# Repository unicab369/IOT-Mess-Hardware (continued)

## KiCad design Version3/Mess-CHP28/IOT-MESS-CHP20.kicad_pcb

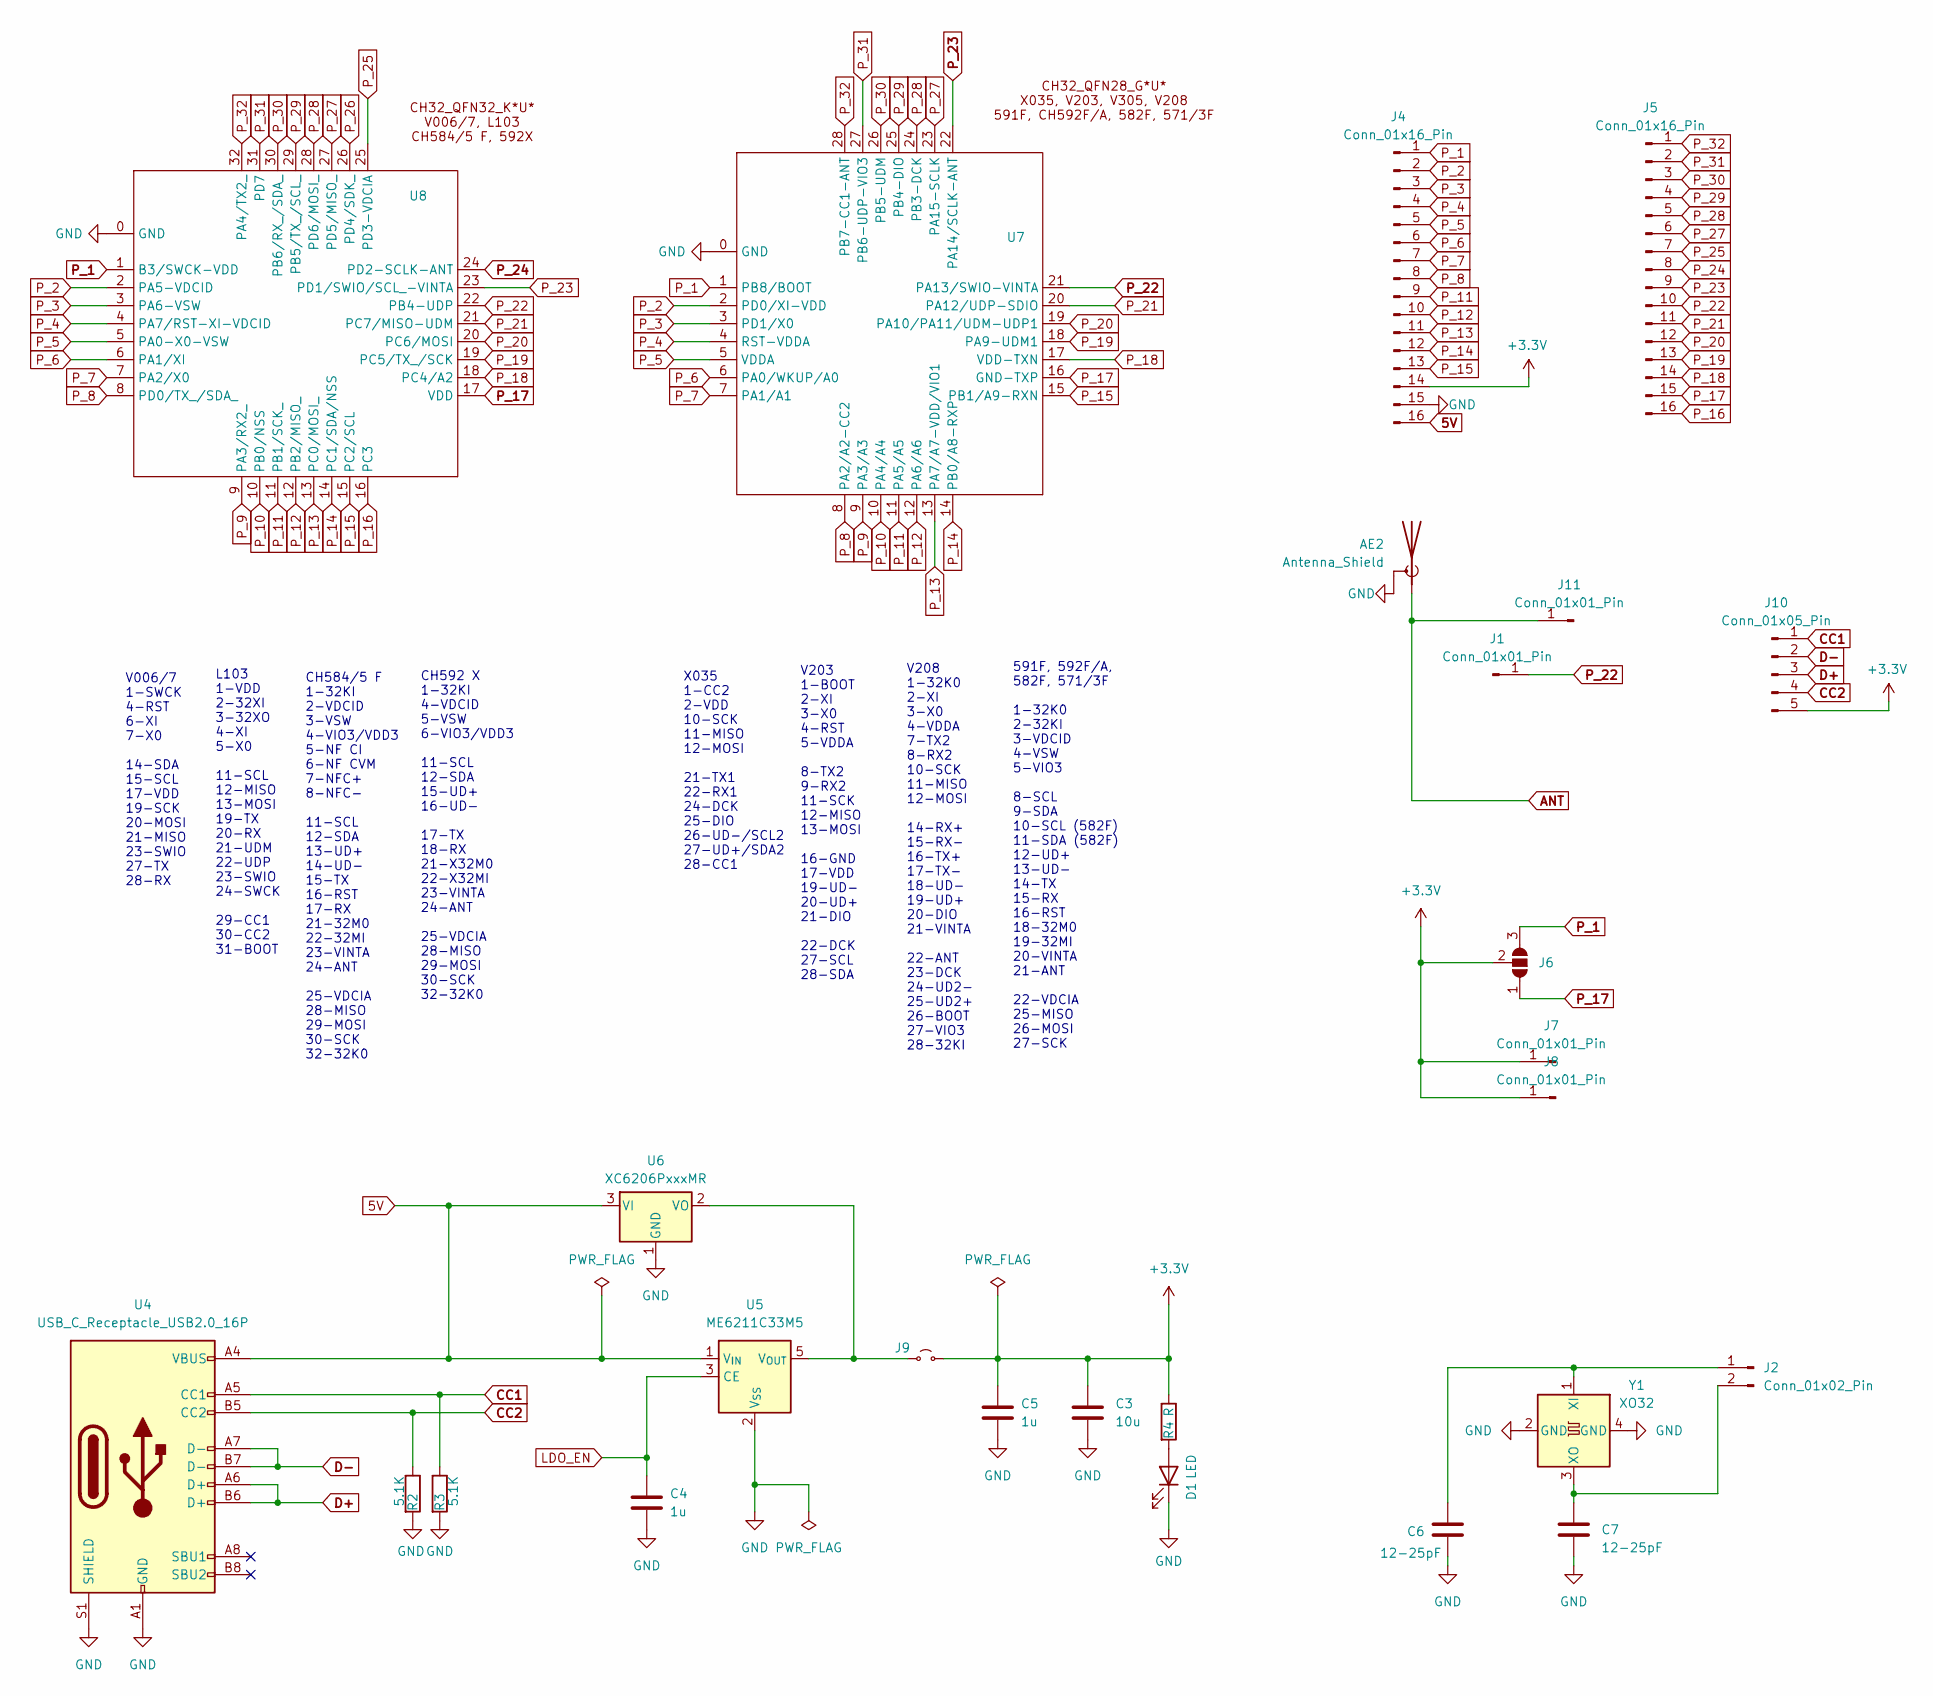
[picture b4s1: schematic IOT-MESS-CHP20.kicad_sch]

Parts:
AE2: Antenna_Shield; Texas_SWRA117D_2.4GHz_Left
C3: 10u; C_0603_1608Metric
C4, C5: 1u; C_0603_1608Metric
C6, C7: 12-25pF; C_0603_1608Metric
D1: LED; LED_0603_1608Metric
J1, J7, J8, J11: Conn_01x01_Pin; PinHeader_1x01_P1.00mm_Vertical
J2: Conn_01x02_Pin; PinHeader_1x02_P1.27mm_Vertical
J4, J5: Conn_01x16_Pin; PinHeader_1x16_P2.54mm_Vertical
J6: Jumper; Jumper-3_P1.3mm_Open_RoundedPad1.0x1.5mm
J9: Jumper_2; Jumpper-triangle
J10: Conn_01x05_Pin; PinHeader_1x05_P1.27mm_Vertical
R2, R3: 5.1K; R_0603_1608Metric
R4: R; R_0603_1608Metric
U4: USB_C_Receptacle_USB2.0_16P; USB_C_Receptacle_HRO_TYPE-C-31-M-12
U5: ME6211C33M5; SOT-23-5
U6: XC6206PxxxMR; SOT-23-3
U7: QFN-28-1EP_4x4mm_P0.4mm_EP2.4x2.4mm_ThermalVias
U8: QFN-32-1EP_4x4mm_P0.4mm_EP2.65x2.65mm_ThermalVias
Y1: XO32; Oscillator_SMD_EuroQuartz_XO32-4Pin_3.2x2.5mm

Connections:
5V: J4.16, U4.A4 (VBUS), U4.A9 (VBUS), U4.B4 (VBUS), U4.B9 (VBUS), U5.1 (V_{IN}), U6.3 (VI)
+3.3V: C3.1, C5.1, J4.14, J6.2 (C), J7.1, J8.1, J9.2 (B), J10.5, R4.1
ANT: AE2.1 (A), J11.1
CC1: J10.1, R3.1, U4.A5 (CC1)
CC2: J10.4, R2.1, U4.B5 (CC2)
D+: J10.3, U4.A6 (D+), U4.B6 (D+)
D-: J10.2, U4.A7 (D-), U4.B7 (D-)
GND: AE2.2 (Shield), C3.2, C4.2, C5.2, C6.2, C7.2, D1.1 (K), J4.15, R2.2, R3.2, U4.A1 (GND), U4.A12 (GND), U4.B1 (GND), U4.B12 (GND), U4.S1 (SHIELD), U5.2 (V_{SS}), U6.1 (GND), U7.0 (GND), U8.0 (GND), Y1.2 (GND), Y1.4 (GND)
LDO_EN: C4.1, U5.3 (CE)
unnamed: D1.2 (A), R4.2
unnamed: C6.1, J2.1, Y1.1 (XI)
unnamed: C7.1, J2.2, Y1.3 (XO)
unnamed: J9.1 (A), U5.5 (V_{OUT}), U6.2 (VO)
P_1: J4.1, J6.3 (B), U7.1 (PB8/BOOT), U8.1 (B3/SWCK-VDD)
P_2: J4.2, U7.2 (PD0/XI-VDD), U8.2 (PA5-VDCID)
P_3: J4.3, U7.3 (PD1/X0), U8.3 (PA6-VSW)
P_4: J4.4, U7.4 (RST-VDDA), U8.4 (PA7/RST-XI-VDCID)
P_5: J4.5, U7.5 (VDDA), U8.5 (PA0-X0-VSW)
P_6: J4.6, U7.6 (PA0/WKUP/A0), U8.6 (PA1/XI)
P_7: J4.7, U7.7 (PA1/A1), U8.7 (PA2/X0)
P_8: J4.8, U7.8 (PA2/A2-CC2), U8.8 (PD0/TX_/SDA_)
P_9: U7.9 (PA3/A3), U8.9 (PA3/RX2_)
P_10: U7.10 (PA4/A4), U8.10 (PB0/NSS)
P_11: J4.9, U7.11 (PA5/A5), U8.11 (PB1/SCK_)
P_12: J4.10, U7.12 (PA6/A6), U8.12 (PB2/MISO_)
P_13: J4.11, U7.13 (PA7/A7-VDD/VIO1), U8.13 (PC0/MOSI_)
P_14: J4.12, U7.14 (PB0/A8-RXP), U8.14 (PC1/SDA/NSS)
P_15: J4.13, U7.15 (PB1/A9-RXN), U8.15 (PC2/SCL)
P_16: J5.16, U8.16 (PC3)
P_17: J5.15, J6.1 (A), U7.16 (GND-TXP), U8.17 (VDD)
P_18: J5.14, U7.17 (VDD-TXN), U8.18 (PC4/A2)
P_19: J5.13, U7.18 (PA9-UDM1), U8.19 (PC5/TX_/SCK)
P_20: J5.12, U7.19 (PA10/PA11/UDM-UDP1), U8.20 (PC6/MOSI)
P_21: J5.11, U7.20 (PA12/UDP-SDIO), U8.21 (PC7/MISO-UDM)
P_22: J1.1, J5.10, U7.21 (PA13/SWIO-VINTA), U8.22 (PB4-UDP)
P_23: J5.9, U7.22 (PA14/SCLK-ANT), U8.23 (PD1/SWIO/SCL_-VINTA)
P_24: J5.8, U8.24 (PD2-SCLK-ANT)
P_25: J5.7, U8.25 (PD3-VDCIA)
P_26: U8.26 (PD4/SDK_)
P_27: J5.6, U7.23 (PA15-SCLK), U8.27 (PD5/MISO_)
P_28: J5.5, U7.24 (PB3-DCK), U8.28 (PD6/MOSI_)
P_29: J5.4, U7.25 (PB4-DIO), U8.29 (PB5/TX_/SCL_)
P_30: J5.3, U7.26 (PB5-UDM), U8.30 (PB6/RX_/SDA_)
P_31: J5.2, U7.27 (PB6-UDP-VIO3), U8.31 (PD7)
P_32: J5.1, U7.28 (PB7-CC1-ANT), U8.32 (PA4/TX2_)

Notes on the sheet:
V203 1-BOOT 2-XI 3-X0 4-RST 5-VDDA 8-TX2 9-RX2 11-SCK 12-MISO 13-MOSI 16-GND 17-VDD 19-UD- 20-UD+ 21-DIO 22-DCK 27-SCL 28-SDA
CH584/5 F 1-32KI 2-VDCID 3-VSW 4-VIO3/VDD3 5-NF CI 6-NF CVM 7-NFC+ 8-NFC- 11-SCL 12-SDA 13-UD+ 14-UD- 15-TX 16-RST 17-RX 21-32M0 22-32MI 23-VINTA 24-ANT 25-VDCIA 28-MISO 29-MOSI 30-SCK 32-32K0
X035 1-CC2 2-VDD 10-SCK 11-MISO 12-MOSI 21-TX1 22-RX1 24-DCK 25-DIO 26-UD-/SCL2 27-UD+/SDA2 28-CC1
L103 1-VDD 2-32XI 3-32XO 4-XI 5-X0 11-SCL 12-MISO 13-MOSI 19-TX 20-RX 21-UDM 22-UDP 23-SWIO 24-SWCK 29-CC1 30-CC2 31-BOOT
V006/7 1-SWCK 4-RST 6-XI 7-X0 14-SDA 15-SCL 17-VDD 19-SCK 20-MOSI 21-MISO 23-SWIO 27-TX 28-RX
CH592 X 1-32KI 4-VDCID 5-VSW 6-VIO3/VDD3 11-SCL 12-SDA 15-UD+ 16-UD- 17-TX 18-RX 21-X32M0 22-X32MI 23-VINTA 24-ANT 25-VDCIA 28-MISO 29-MOSI 30-SCK 32-32K0
V208 1-32K0 2-XI 3-X0 4-VDDA 7-TX2 8-RX2 10-SCK 11-MISO 12-MOSI 14-RX+ 15-RX- 16-TX+ 17-TX- 18-UD- 19-UD+ 20-DIO 21-VINTA 22-ANT 23-DCK 24-UD2- 25-UD2+ 26-BOOT 27-VIO3 28-32KI
591F, 592F/A, 582F, 571/3F 1-32K0 2-32KI 3-VDCID 4-VSW 5-VIO3 8-SCL 9-SDA 10-SCL (582F) 11-SDA (582F) 12-UD+ 13-UD- 14-TX 15-RX 16-RST 18-32M0 19-32MI 20-VINTA 21-ANT 22-VDCIA 25-MISO 26-MOSI 27-SCK

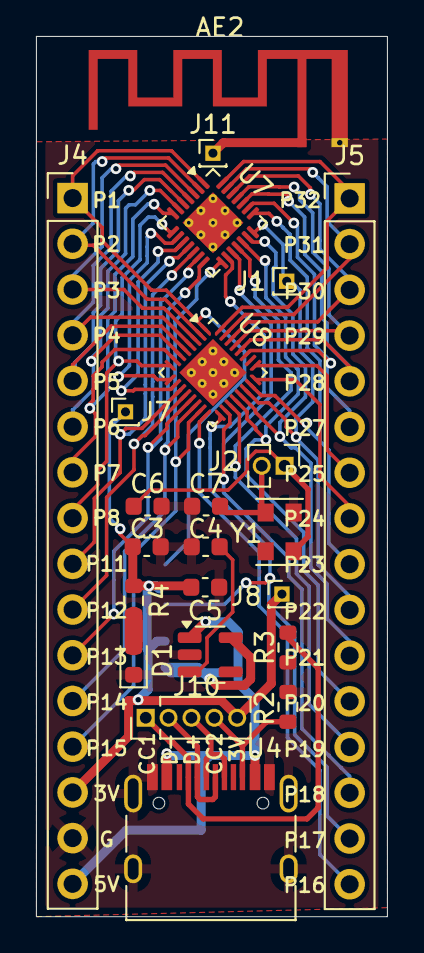
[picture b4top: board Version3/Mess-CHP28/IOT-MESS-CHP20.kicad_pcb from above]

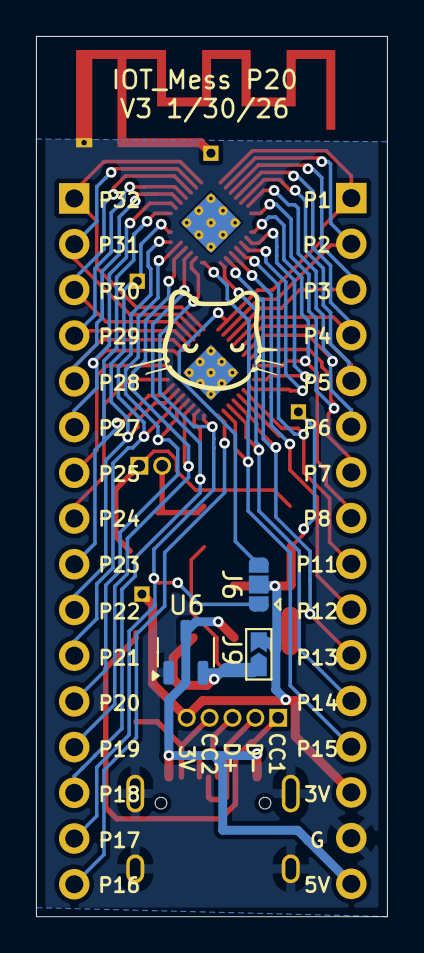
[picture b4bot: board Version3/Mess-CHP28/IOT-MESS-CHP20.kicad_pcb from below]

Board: 2 copper layers, 19.5 x 48.9 mm, 26 parts (3 on the bottom side), 44 nets.

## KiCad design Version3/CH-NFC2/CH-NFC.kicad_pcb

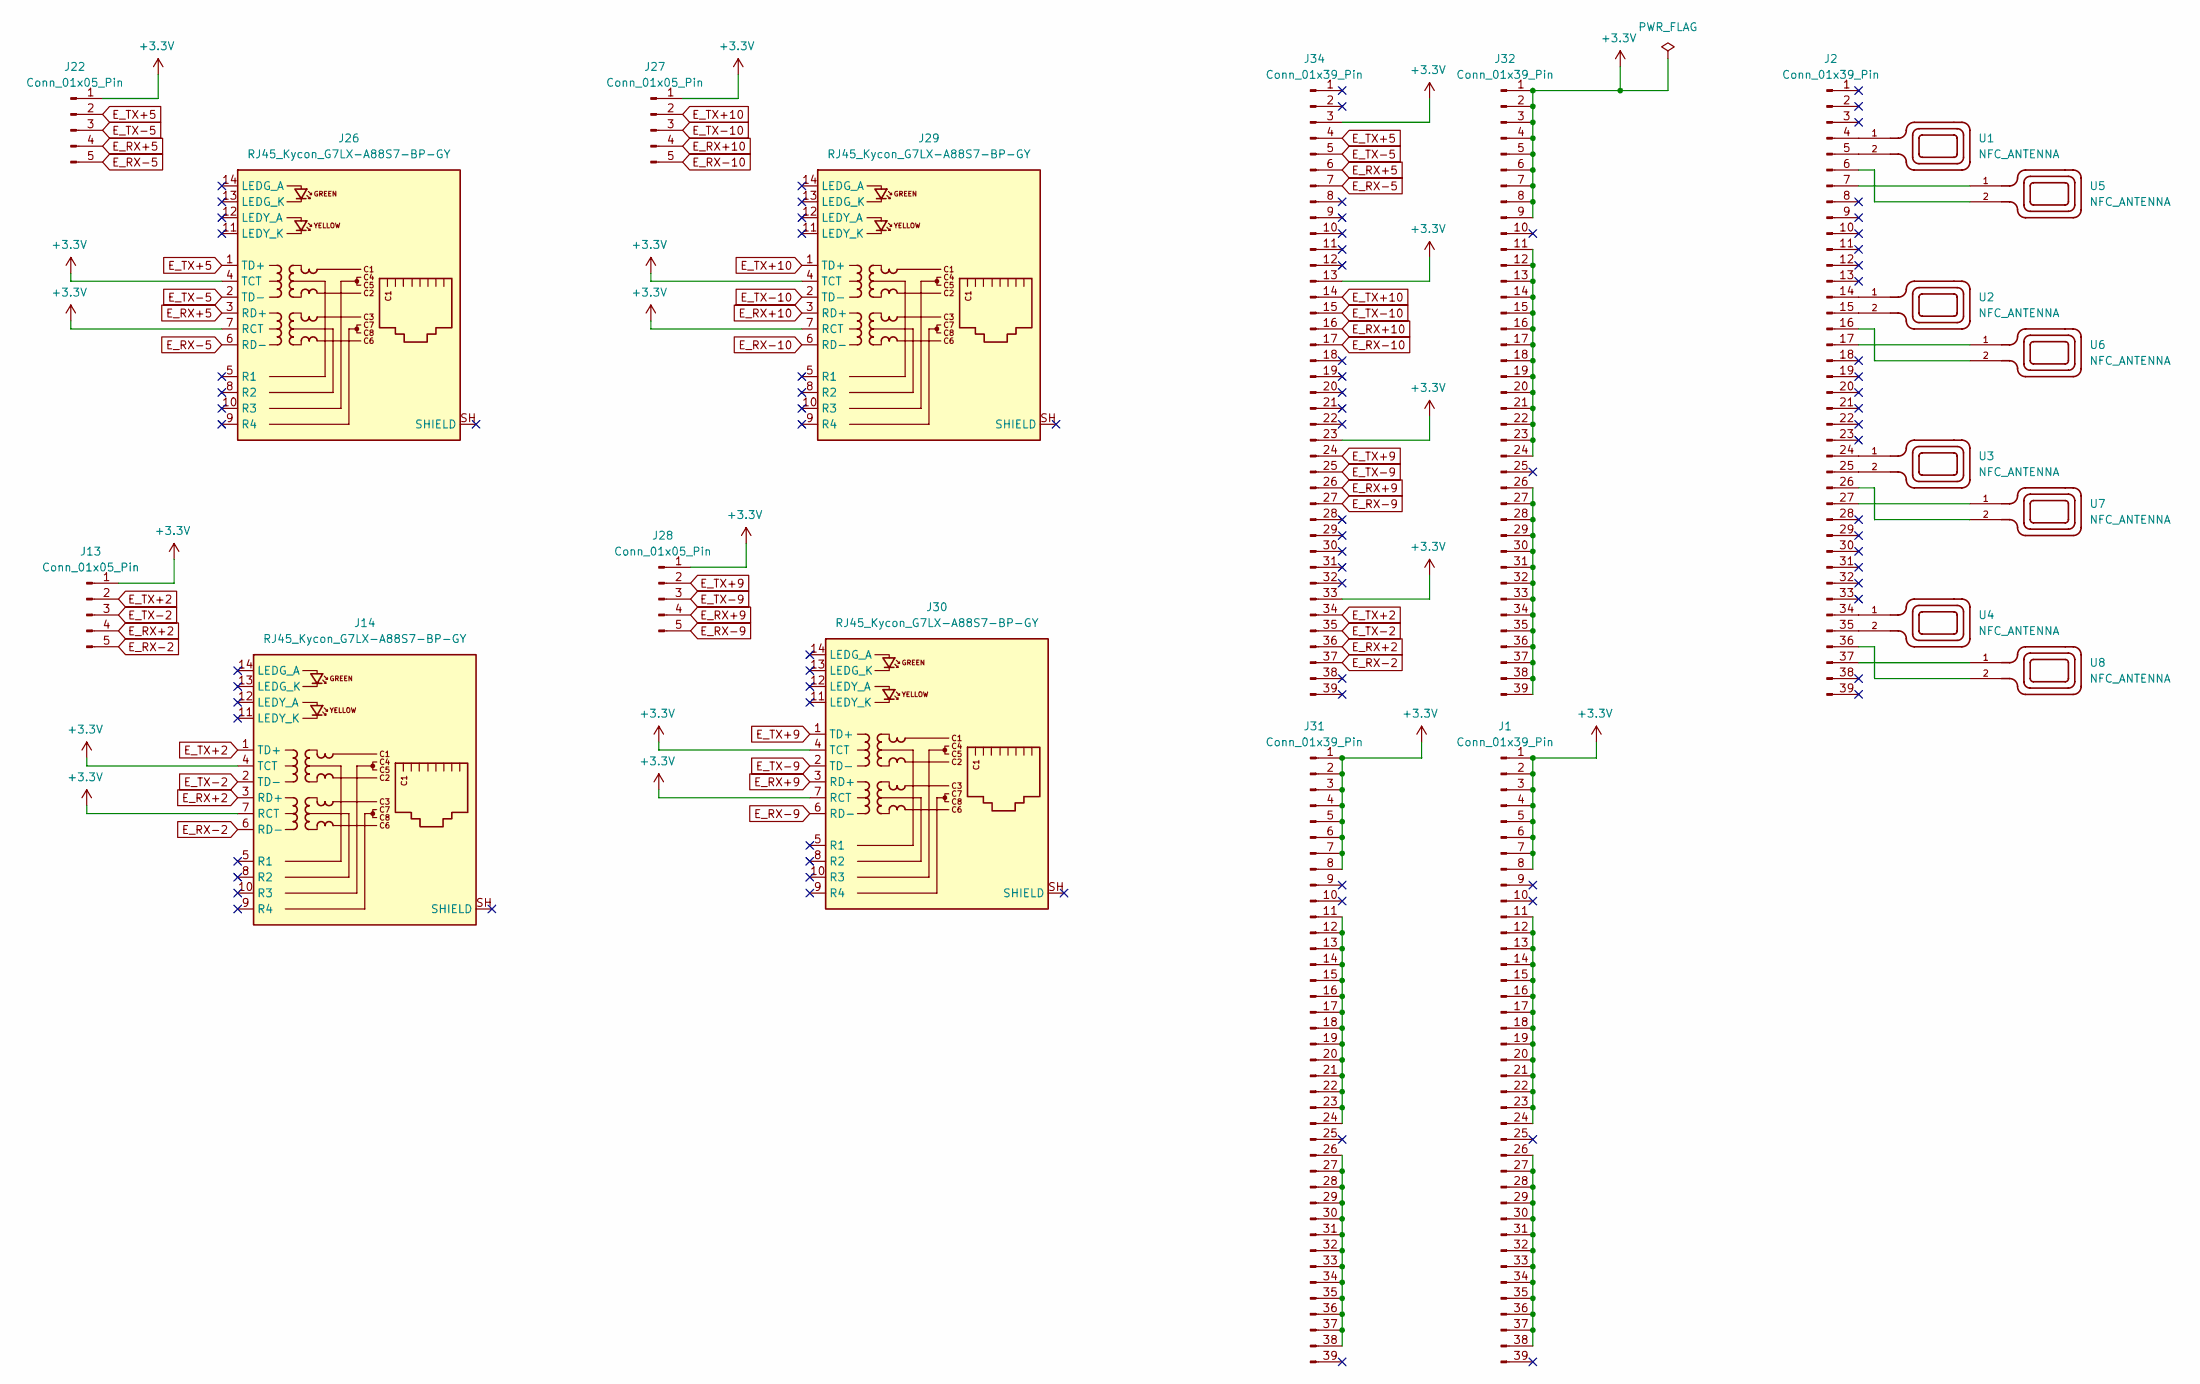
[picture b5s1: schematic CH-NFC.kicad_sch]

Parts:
J1, J2, J31, J32, J34: Conn_01x39_Pin; PinHeader_1x39_P2.54mm_Vertical
J13, J22, J27, J28: Conn_01x05_Pin; PinHeader_1x05_P2.54mm_Vertical
J14, J26, J29, J30: RJ45_Kycon_G7LX-A88S7-BP-GY; RJ45_Kycon_G7LX-A88S7-BP-xx_Horizontal
U1, U2, U3, U4, U5, U6, U7, U8: NFC_ANTENNA; NFC_ANT

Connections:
+3.3V: J1.1, J1.2, J1.3, J1.4, J1.5, J1.6, J1.7, J1.8, J13.1, J14.4 (TCT), J14.7 (RCT), J22.1, J26.4 (TCT), J26.7 (RCT), J27.1, J28.1, J29.4 (TCT), J29.7 (RCT), J30.4 (TCT), J30.7 (RCT), J31.1, J31.2, J31.3, J31.4, J31.5, J31.6, J31.7, J31.8, J32.1, J32.2, J32.3, J32.4, J32.5, J32.6, J32.7, J32.8, J32.9, J34.3, J34.13, J34.23, J34.33
E_RX+2: J13.4, J14.3 (RD+), J34.36
E_RX+5: J22.4, J26.3 (RD+), J34.6
E_RX+9: J28.4, J30.3 (RD+), J34.26
E_RX+10: J27.4, J29.3 (RD+), J34.16
E_RX-2: J13.5, J14.6 (RD-), J34.37
E_RX-5: J22.5, J26.6 (RD-), J34.7
E_RX-9: J28.5, J30.6 (RD-), J34.27
E_RX-10: J27.5, J29.6 (RD-), J34.17
E_TX+2: J13.2, J14.1 (TD+), J34.34
E_TX+5: J22.2, J26.1 (TD+), J34.4
E_TX+9: J28.2, J30.1 (TD+), J34.24
E_TX+10: J27.2, J29.1 (TD+), J34.14
E_TX-2: J13.3, J14.2 (TD-), J34.35
E_TX-5: J22.3, J26.2 (TD-), J34.5
E_TX-9: J28.3, J30.2 (TD-), J34.25
E_TX-10: J27.3, J29.2 (TD-), J34.15
unnamed: J1.11, J1.12, J1.13, J1.14, J1.15, J1.16, J1.17, J1.18, J1.19, J1.20, J1.21, J1.22, J1.23, J1.24
unnamed: J1.26, J1.27, J1.28, J1.29, J1.30, J1.31, J1.32, J1.33, J1.34, J1.35, J1.36, J1.37, J1.38
unnamed: J2.4, U1.1
unnamed: J2.5, U1.2
unnamed: J2.6, U5.2
unnamed: J2.7, U5.1
unnamed: J2.14, U2.1
unnamed: J2.15, U2.2
unnamed: J2.16, U6.2
unnamed: J2.17, U6.1
unnamed: J2.24, U3.1
unnamed: J2.25, U3.2
unnamed: J2.26, U7.2
unnamed: J2.27, U7.1
unnamed: J2.34, U4.1
unnamed: J2.35, U4.2
unnamed: J2.36, U8.2
unnamed: J2.37, U8.1
unnamed: J31.11, J31.12, J31.13, J31.14, J31.15, J31.16, J31.17, J31.18, J31.19, J31.20, J31.21, J31.22, J31.23, J31.24
unnamed: J31.26, J31.27, J31.28, J31.29, J31.30, J31.31, J31.32, J31.33, J31.34, J31.35, J31.36, J31.37, J31.38
unnamed: J32.11, J32.12, J32.13, J32.14, J32.15, J32.16, J32.17, J32.18, J32.19, J32.20, J32.21, J32.22, J32.23, J32.24
unnamed: J32.26, J32.27, J32.28, J32.29, J32.30, J32.31, J32.32, J32.33, J32.34, J32.35, J32.36, J32.37, J32.38, J32.39

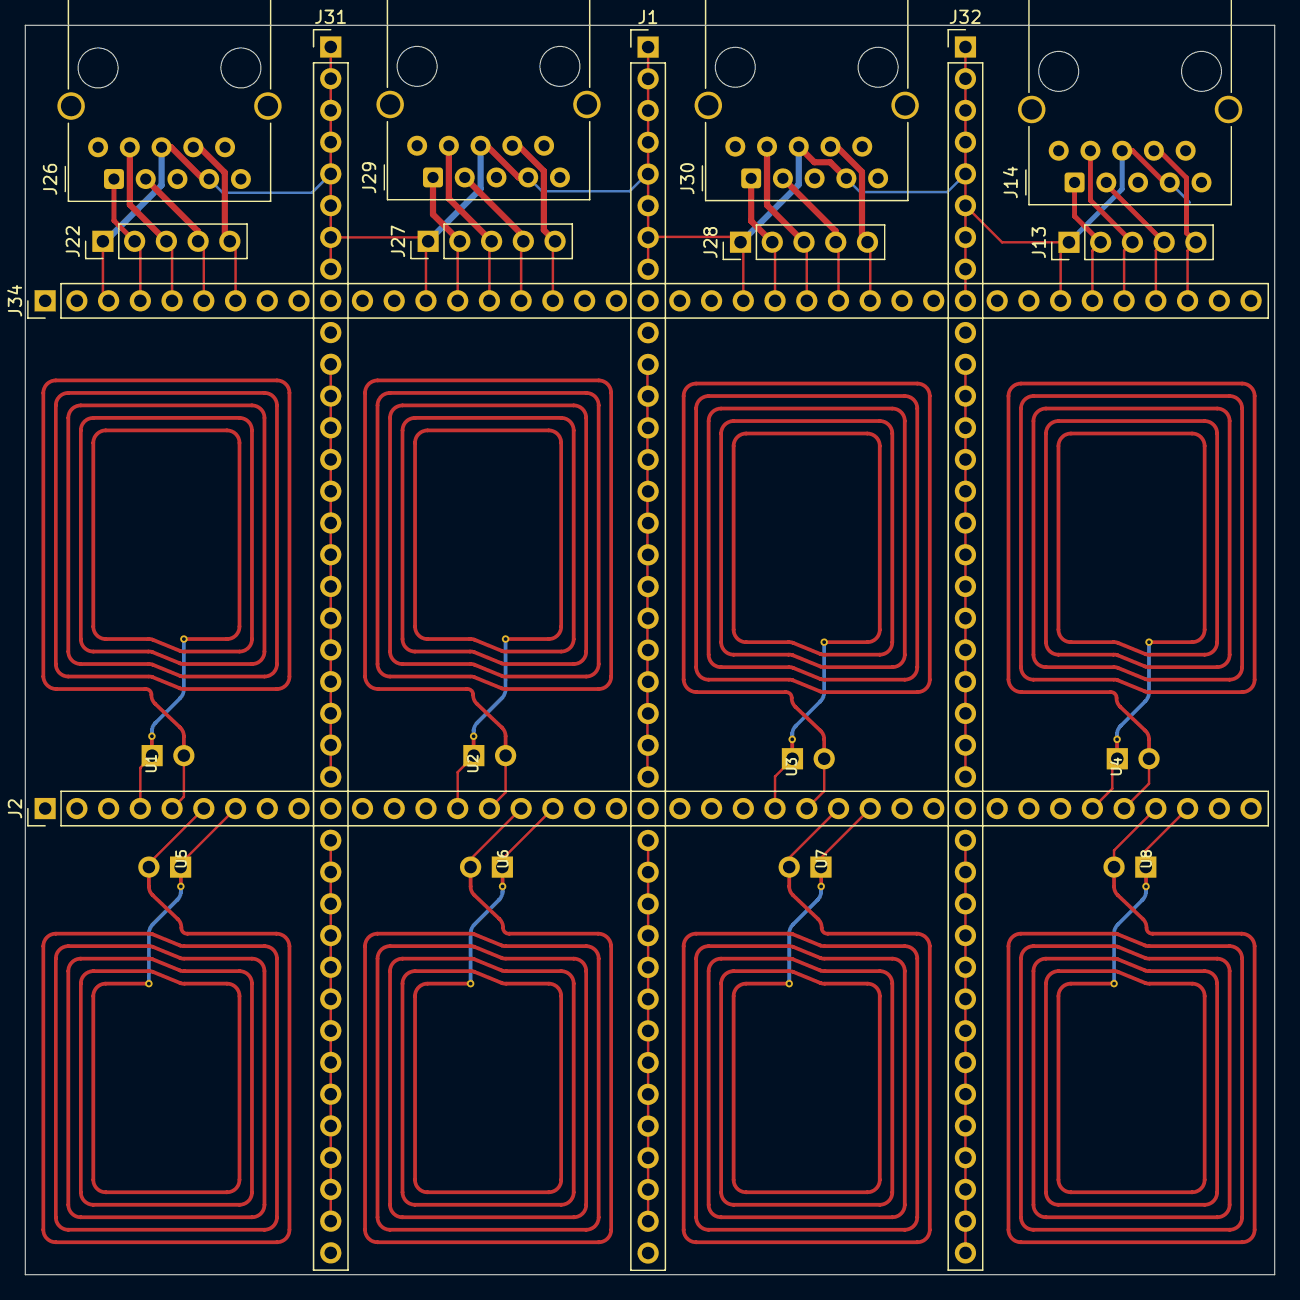
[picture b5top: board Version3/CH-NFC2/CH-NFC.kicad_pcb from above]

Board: 2 copper layers, 100.0 x 100.0 mm, 21 parts (0 on the bottom side), 39 nets.

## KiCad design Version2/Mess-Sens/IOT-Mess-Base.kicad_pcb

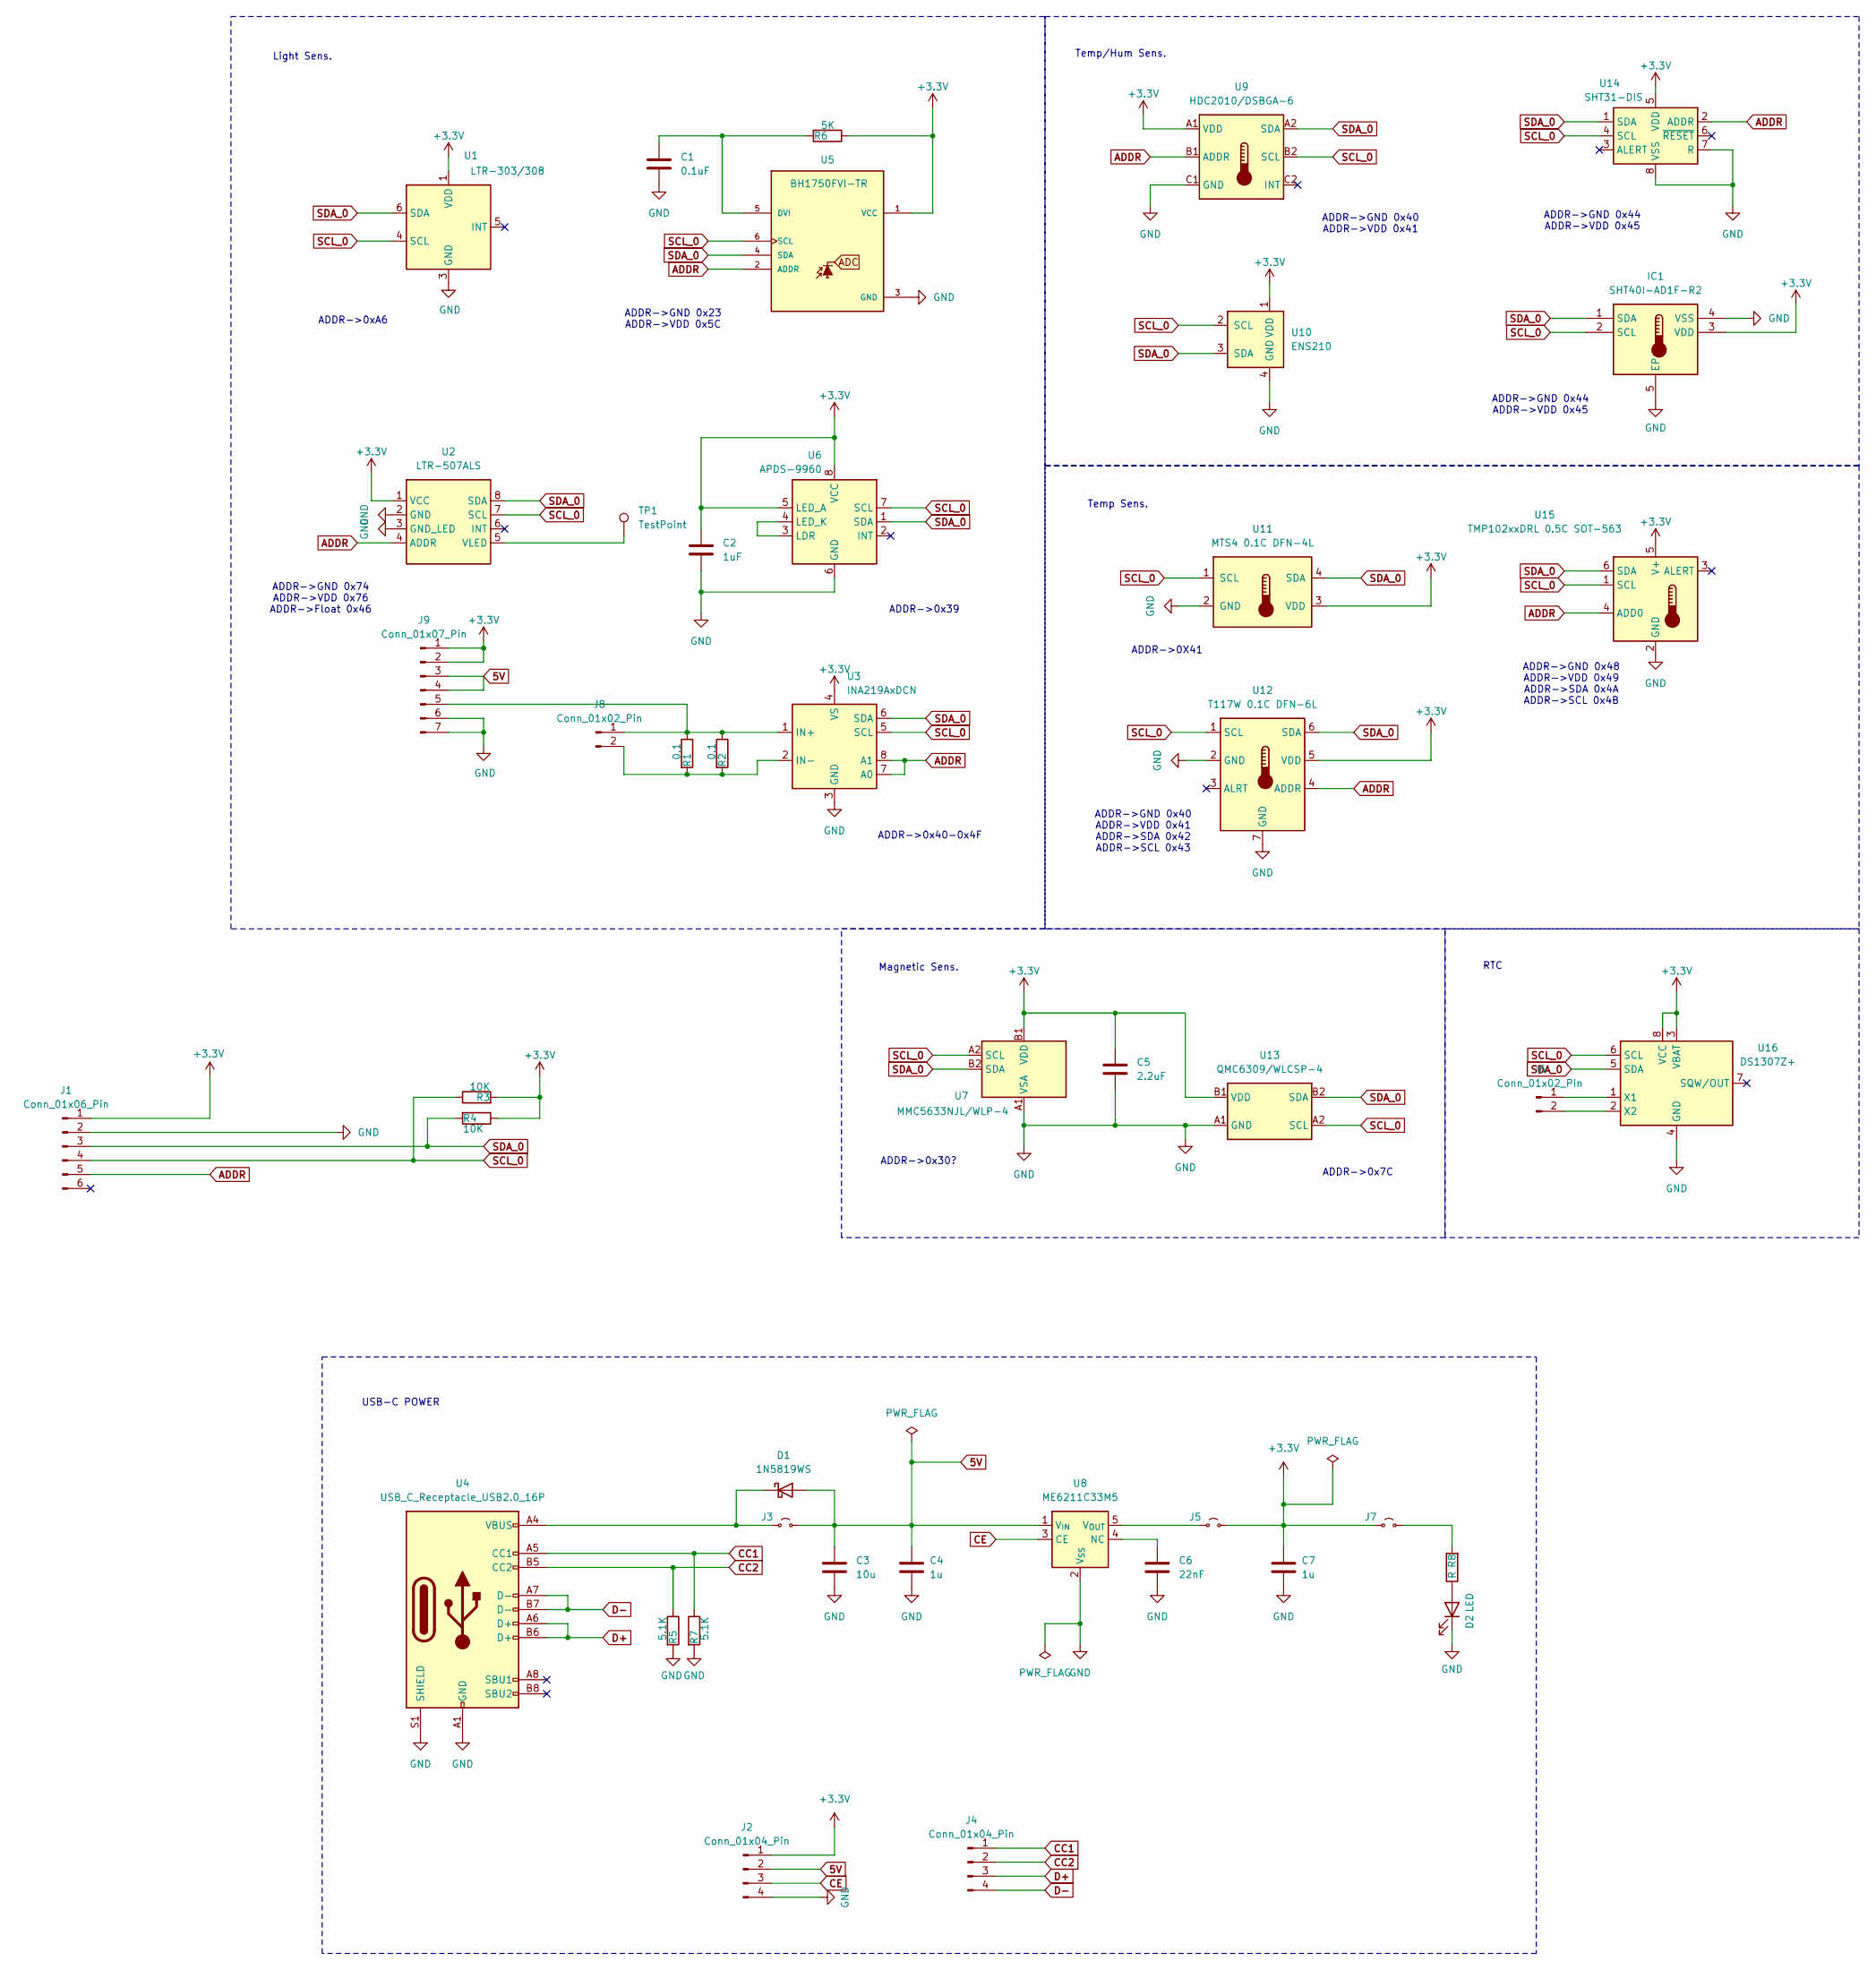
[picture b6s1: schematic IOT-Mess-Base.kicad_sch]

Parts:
C1: 0.1uF; C_0603_1608Metric
C2: 1uF; C_0603_1608Metric
C3: 10u; C_0603_1608Metric
C4, C7: 1u; C_0603_1608Metric
C5: 2.2uF; C_0603_1608Metric
C6: 22nF; C_0603_1608Metric
D1: 1N5819WS; D_SOD-323
D2: LED; LED_0603_1608Metric
IC1: SHT40I-AD1F-R2; SON80P150X150X59-5N; Mouser Part Number 403-SHT40I-AD1F-R2
J1: Conn_01x06_Pin; PinHeader_1x06_P2.54mm_Vertical
J2, J4: Conn_01x04_Pin; PinHeader_1x04_P2.54mm_Vertical
J3, J5, J7: Jumper_2; Jumpper-triangle
J6: Conn_01x02_Pin; PinHeader_1x02_P1.27mm_Vertical
J8: Conn_01x02_Pin; PinHeader_1x02_P2.54mm_Vertical
J9: Conn_01x07_Pin; PinHeader_1x07_P2.54mm_Vertical
R1: 0.1; R_2512_6332Metric
R2: 0.1; R_1206_3216Metric
R3, R4: 10K; R_0603_1608Metric
R5, R7: 5.1K; R_0603_1608Metric
R6: 5K; R_0603_1608Metric
R8: R; R_0603_1608Metric
TP1: TestPoint; PinHeader_1x01_P1.00mm_Vertical
U1: LTR-303/308; Lite-On_LTR-303ALS-01
U2: LTR-507ALS
U3: INA219AxDCN; SOT-23-8
U4: USB_C_Receptacle_USB2.0_16P; USB_C_Receptacle_HRO_TYPE-C-31-M-12
U5: BH1750FVI-TR; XDCR_BH1750FVI-TR
U6: APDS-9960; Avago_APDS-9960
U7: MMC5633NJL/WLP-4; WLP-4_0.86x0.86mm_P0.4mm
U8: ME6211C33M5; SOT-23-5
U9: HDC2010/DSBGA-6; BGA6C100X50P2X3_HDC2010YPAR
U10: ENS210; AMS_QFN-4-1EP_2x2mm_P0.95mm_EP0.7x1.6mm
U11: MTS4 0.1C DFN-4L; DFN-4L
U12: T117W 0.1C DFN-6L; DFN-6L
U13: QMC6309/WLCSP-4; WLCSP-4_0.8x0.8mm_Layout2x2_P0.4mm
U14: SHT31-DIS; Sensirion_DFN-8-1EP_2.5x2.5mm_P0.5mm_EP1.1x1.7mm
U15: TMP102xxDRL 0.5C SOT-563; SOT-563
U16: DS1307Z+; SOIC-8_3.9x4.9mm_P1.27mm

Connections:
5V: C3.1, C4.1, D1.2 (A), J2.2, J3.2 (B), J9.3, J9.4, U8.1 (V_{IN})
+3.3V: C2.1, C5.1, C7.1, IC1.3 (VDD), J1.1, J2.1, J5.2 (B), J7.1 (A), J9.1, J9.2, R3.2, R4.1, R6.1, U1.1 (VDD), U2.1 (VCC), U3.4 (VS), U5.1 (VCC), U6.5 (LED_A), U6.8 (VCC), U7.B1 (VDD), U9.A1 (VDD), U10.1 (VDD), U11.3 (VDD), U12.5 (VDD), U13.B1 (VDD), U14.5 (VDD), U15.5 (V+), U16.3 (VBAT), U16.8 (VCC)
ADDR: J1.5, U2.4 (ADDR), U3.7 (A0), U3.8 (A1), U5.2 (ADDR), U9.B1 (ADDR), U12.4 (ADDR), U14.2 (ADDR), U15.4 (ADD0)
CC1: J4.1, R7.1, U4.A5 (CC1)
CC2: J4.2, R5.1, U4.B5 (CC2)
CE: J2.3, U8.3 (CE)
D+: J4.3, U4.A6 (D+), U4.B6 (D+)
D-: J4.4, U4.A7 (D-), U4.B7 (D-)
GND: C1.2, C2.2, C3.2, C4.2, C5.2, C6.2, C7.2, D2.1 (K), IC1.4 (VSS), IC1.5 (EP), J1.2, J2.4, J9.6, J9.7, R5.2, R7.2, U1.3 (GND), U2.2 (GND), U2.3 (GND_LED), U3.3 (GND), U4.A1 (GND), U4.A12 (GND), U4.B1 (GND), U4.B12 (GND), U4.S1 (SHIELD), U5.3 (GND), U6.6 (GND), U7.A1 (VSA), U8.2 (V_{SS}), U9.C1 (GND), U10.4 (GND), U10.5 (GND), U11.2 (GND), U12.2 (GND), U12.7 (GND), U13.A1 (GND), U14.7 (R), U14.8 (VSS), U14.9 (VSS), U15.2 (GND), U16.4 (GND)
unnamed: D1.1 (K), J3.1 (A), U4.A4 (VBUS), U4.A9 (VBUS), U4.B4 (VBUS), U4.B9 (VBUS)
unnamed: D2.2 (A), R8.1
unnamed: J5.1 (A), U8.5 (V_{OUT})
unnamed: J6.1, U16.1 (X1)
unnamed: J6.2, U16.2 (X2)
unnamed: J7.2 (B), R8.2
unnamed: J8.1, J9.5, R1.1, R2.1, U3.1 (IN+)
unnamed: J8.2, R1.2, R2.2, U3.2 (IN-)
unnamed: TP1.1, U2.5 (VLED)
unnamed: C1.1, R6.2, U5.5 (DVI)
unnamed: U6.3 (LDR), U6.4 (LED_K)
unnamed: C6.1, U8.4 (NC)
SCL_0: IC1.2 (SCL), J1.4, R3.1, U1.4 (SCL), U2.7 (SCL), U3.5 (SCL), U5.6 (SCL), U6.7 (SCL), U7.A2 (SCL), U9.B2 (SCL), U10.2 (SCL), U11.1 (SCL), U12.1 (SCL), U13.A2 (SCL), U14.4 (SCL), U15.1 (SCL), U16.6 (SCL)
SDA_0: IC1.1 (SDA), J1.3, R4.2, U1.6 (SDA), U2.8 (SDA), U3.6 (SDA), U5.4 (SDA), U6.1 (SDA), U7.B2 (SDA), U9.A2 (SDA), U10.3 (SDA), U11.4 (SDA), U12.6 (SDA), U13.B2 (SDA), U14.1 (SDA), U15.6 (SDA), U16.5 (SDA)

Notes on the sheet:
ADDR->0x40-0x4F
USB-C POWER
Light Sens.
RTC
ADDR->GND 0x40 ADDR->VDD 0x41
ADDR->GND 0x48 ADDR->VDD 0x49 ADDR->SDA 0x4A ADDR->SCL 0x4B
ADDR->0x39
ADDR->GND 0x44 ADDR->VDD 0x45
ADDR->0x7C
Temp Sens.
ADDR->0X41
ADDR->GND 0x40 ADDR->VDD 0x41 ADDR->SDA 0x42 ADDR->SCL 0x43
ADDR->0xA6
Magnetic Sens.
ADDR->0x30?
Temp/Hum Sens.
ADDR->GND 0x23 ADDR->VDD 0x5C
ADDR->GND 0x74 ADDR->VDD 0x76 ADDR->Float 0x46

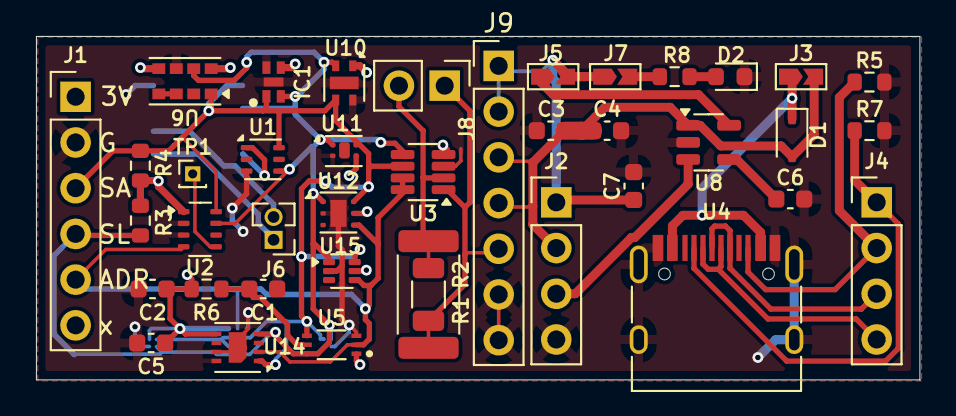
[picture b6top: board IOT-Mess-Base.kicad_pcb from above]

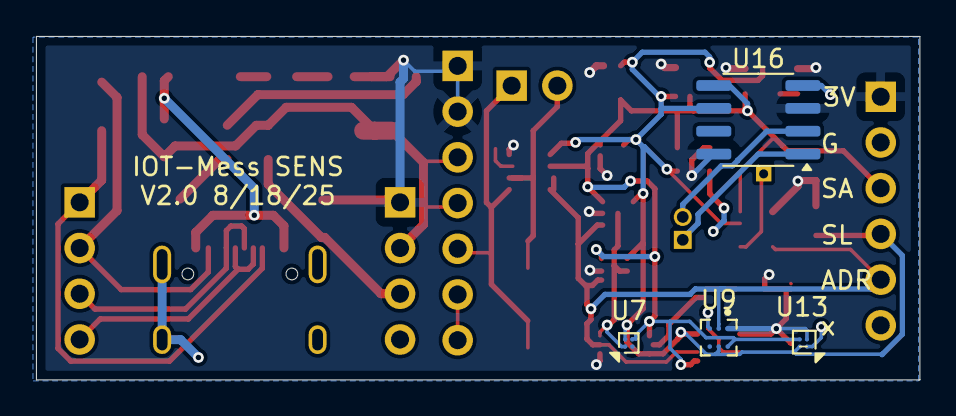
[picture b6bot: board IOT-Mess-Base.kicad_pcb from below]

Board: 2 copper layers, 49.1 x 19.1 mm, 44 parts (4 on the bottom side), 23 nets.

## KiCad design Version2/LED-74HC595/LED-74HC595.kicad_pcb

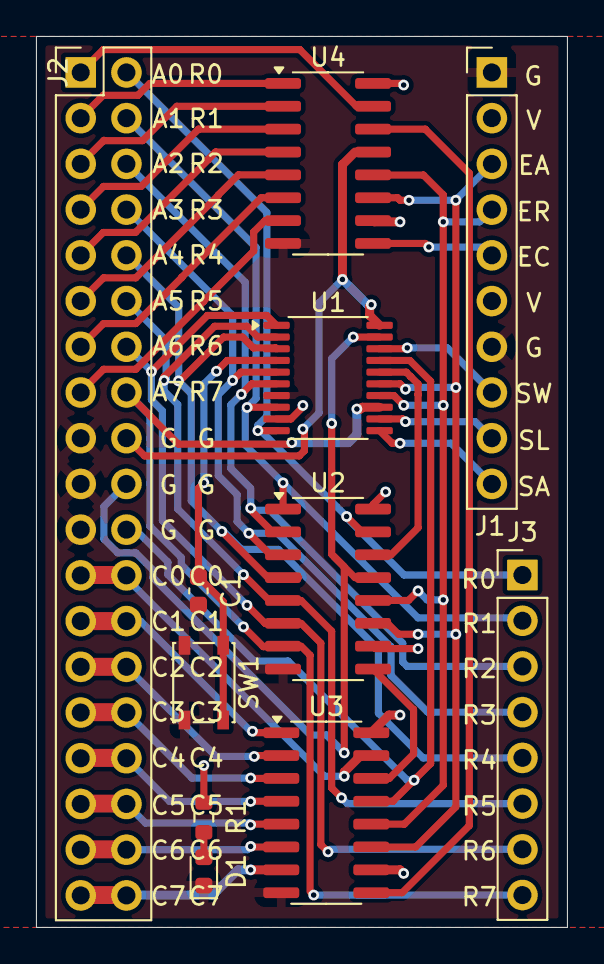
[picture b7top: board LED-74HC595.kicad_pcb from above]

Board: 2 copper layers, 29.5 x 49.5 mm, 11 parts (0 on the bottom side), 40 nets.

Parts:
C1: .1u; C_0603_1608Metric
D1: LED; LED_0603_1608Metric
J1: Conn_01x10_Pin; PinHeader_1x10_P2.54mm_Vertical
J2: Conn_02x19_Odd_Even; PinHeader_2x19_P2.54mm_Vertical
J3: Conn_01x08_Pin; PinHeader_1x08_P2.54mm_Vertical
R1: R; R_0603_1608Metric
SW1: SW_Push; SW_SPST_PTS810
U1: TSSOP-20_4.4x6.5mm_P0.65mm
U2, U3, U4: 74HC595; SOP-16_3.9x9.9mm_P1.27mm

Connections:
A_0: J2.1, U4.15 (QA)
A_1: J2.3, U4.1 (QB)
A_2: J2.5, U4.2 (QC)
A_3: J2.7, U4.3 (QD)
A_4: J2.9, U4.4 (QE)
A_5: J2.11, U4.5 (QF)
A_6: J2.13, U4.6 (QG)
A_7: J2.15, U4.7 (QH)
C0: J2.23, J2.24, U3.15 (QA)
C1: J2.25, J2.26, U3.1 (QB)
C2: J2.27, J2.28, U3.2 (QC)
C3: J2.29, J2.30, U3.3 (QD)
C4: J2.31, J2.32, U3.4 (QE)
C5: J2.33, J2.34, U3.5 (QF)
C6: J2.35, J2.36, U3.6 (QG)
C7: J2.37, J2.38, U3.7 (QH)
CLCK: J1.3, U1.15 (PC5/VSS*), U2.11 (SRCLK), U3.11 (SRCLK), U4.11 (SRCLK)
DATA: U1.16 (PC6/MOSI/VDD*), U2.14 (SER)
EN_A: J2.18, U1.20 (PD3/A4/ANT*), U4.13 (~OE)
EN_C: J2.22, U1.17 (PC7/MISO/UDM*), U3.13 (~OE)
EN_R: J2.20, U1.19 (PD2/A3/SWIO*), U2.13 (~OE)
GND: C1.2, D1.1 (K), J1.1, J1.7, J2.17, J2.19, J2.21, SW1.1, U1.7 (VSS), U2.8 (GND), U3.8 (GND), U4.8 (GND)
LATCH: J1.4, U1.14 (PC4/A2), U2.12 (RCLK), U3.12 (RCLK), U4.12 (RCLK)
unnamed: D1.2 (A), R1.2
unnamed: J1.5, U4.9 (QH')
unnamed: C1.1, SW1.2, U1.4 (PD7/RST)
unnamed: U2.9 (QH'), U3.14 (SER)
unnamed: U3.9 (QH'), U4.14 (SER)
R0: J2.2, J3.1, U1.10 (PC0), U2.15 (QA)
R1: J2.4, J3.2, U1.8 (PD0), U2.1 (QB)
R2: J2.6, J3.3, U1.6 (PA2/OSCO), U2.2 (QC)
R3: J2.8, J3.4, U1.5 (PA1/OSCI), U2.3 (QD)
R4: J2.10, J3.5, U1.3 (PD6/A6/OSCO*), U2.4 (QE)
R5: J2.12, J3.6, U1.2 (PD5/A5/OSCI*), U2.5 (QF)
R6: J2.14, J3.7, U1.1 (PD4/A7), U2.6 (QG)
R7: J2.16, J3.8, U1.13 (PC3), U2.7 (QH)
SCL: J1.9, U1.12 (PC2/SCL)
SDA: J1.10, U1.11 (PC1/SDA)
SWIO: J1.8, U1.18 (PD1/SWIO/UDP*)
VCC: J1.2, J1.6, R1.1, U1.9 (VDD), U2.10 (~SRCLR), U2.16 (VCC), U3.10 (~SRCLR), U3.16 (VCC), U4.10 (~SRCLR), U4.16 (VCC)
